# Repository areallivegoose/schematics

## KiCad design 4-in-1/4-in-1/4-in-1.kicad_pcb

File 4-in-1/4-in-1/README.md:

Each board on a separate schematic, with power on main sheet.
Effect order: DynaComp > Rangemaster > OCD > LPB1

Sources:
+ [Ross DynaComp](https://www.electrosmash.com/mxr-dyna-comp-analysis)
+ [Dallas Rangemaster](https://fuzzcentral.ssguitar.com/rangemaster.php)
+ [Fulltone OCD](http://zadvitsky.com/index.php/projects/pedals/ocd-overdrive-diy.html)
+ [LPB1](https://www.coda-effects.com/p/lpb1-circuit-analysis.html)

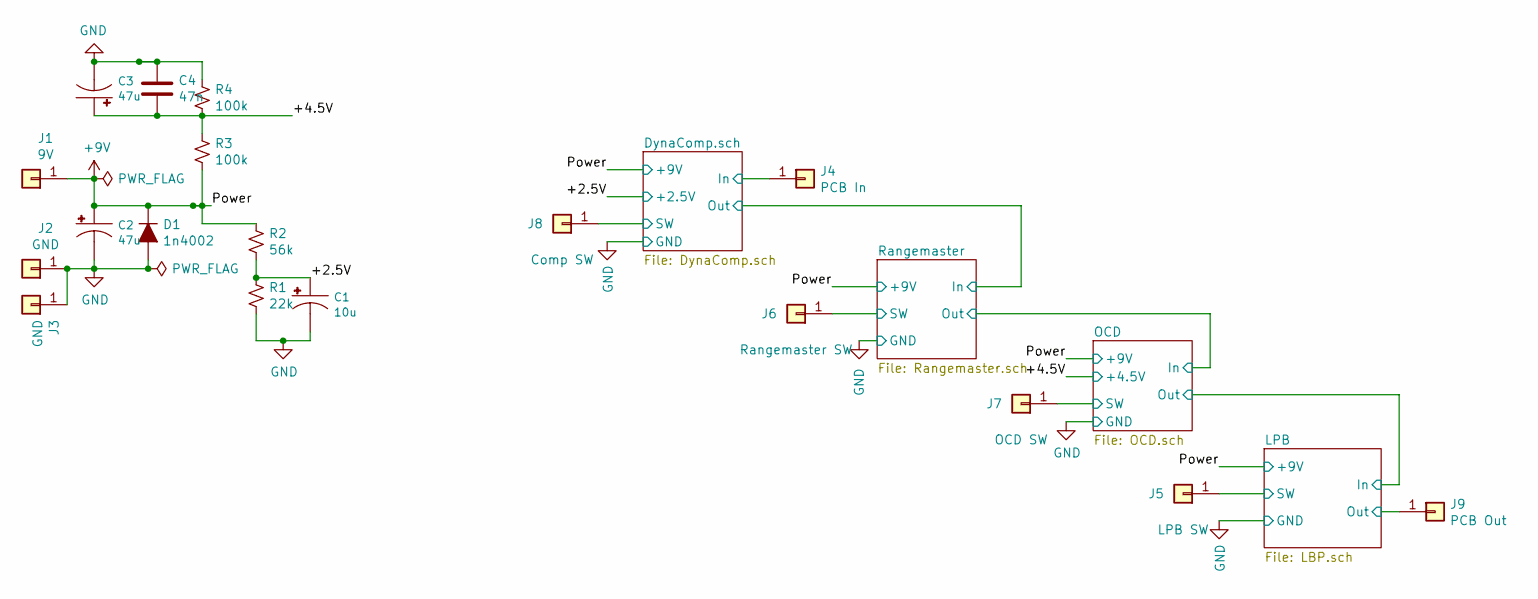
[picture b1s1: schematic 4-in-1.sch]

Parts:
C1: 10u; Cap_Electrolytic_TH
C2, C3: 47u; Cap_Electrolytic_TH
C4: 47n; Cap_Ceramic_TH
D1: 1n4002; Diode_BAT-85S_TH
J1: 9V; WireHole
J2, J3: GND; WireHole
J4: PCB In; WireHole
J5: LPB SW; WireHole
J6: Rangemaster SW; WireHole
J7: OCD SW; WireHole
J8: Comp SW; WireHole
J9: PCB Out; WireHole
R1: 22k; R_Axial_DIN0207_L6.3mm_D2.5mm_P7.62mm_Horizontal
R2: 56k; R_Axial_DIN0207_L6.3mm_D2.5mm_P7.62mm_Horizontal
R3, R4: 100k; R_Axial_DIN0207_L6.3mm_D2.5mm_P7.62mm_Horizontal

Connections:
+9V: C2.1 (+), D1.1 (K), J1.1, R2.1, R3.2; also elsewhere on the board
/+2.5V: C1.1 (+), R1.1, R2.2; also elsewhere on the board
/+4.5V: C3.1 (+), C4.2, R3.1, R4.2; also elsewhere on the board
/DynaComp.sch/In: J4.1; also elsewhere on the board
/DynaComp.sch/SW: J8.1; also elsewhere on the board
/LPB/Out: J9.1; also elsewhere on the board
/LPB/SW: J5.1; also elsewhere on the board
/OCD/SW: J7.1; also elsewhere on the board
/Rangemaster/SW: J6.1; also elsewhere on the board
GND: C1.2 (-), C2.2 (-), C3.2 (-), C4.1, D1.2 (A), J2.1, J3.1, R1.2, R4.1; also elsewhere on the board

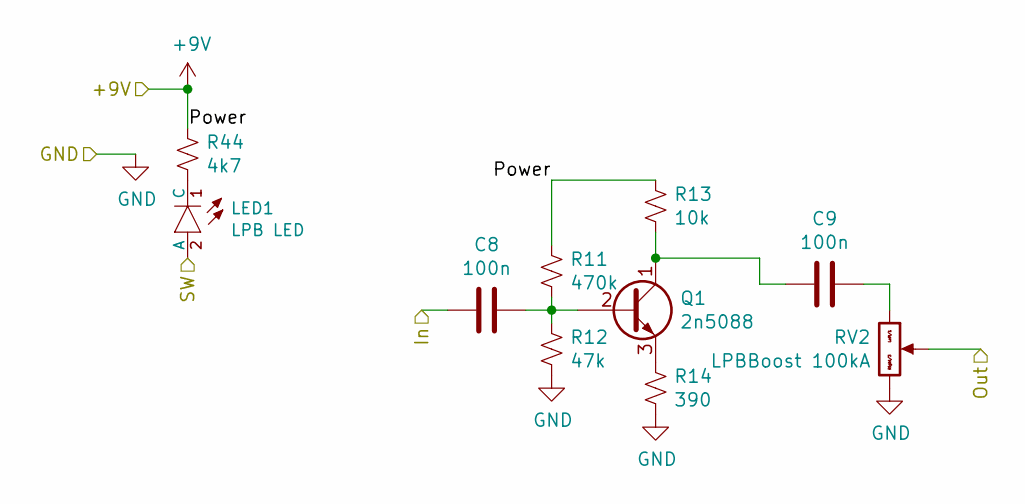
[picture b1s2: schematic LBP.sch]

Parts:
C8, C9: 100n; Cap_Ceramic_TH
LED1: LPB LED; LED-C1-A2-3MM-VERT
Q1: 2n5088; TO-92_Inline_Wide
R11: 470k; R_Axial_DIN0207_L6.3mm_D2.5mm_P7.62mm_Horizontal
R12: 47k; R_Axial_DIN0207_L6.3mm_D2.5mm_P7.62mm_Horizontal
R13: 10k; R_Axial_DIN0207_L6.3mm_D2.5mm_P7.62mm_Horizontal
R14: 390; R_Axial_DIN0207_L6.3mm_D2.5mm_P7.62mm_Horizontal
R44: 4k7; R_Axial_DIN0207_L6.3mm_D2.5mm_P7.62mm_Horizontal
RV2: LPBBoost 100kA; Pot_16mm_NoDet_RV16AF-4A

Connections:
+9V: R11.2, R13.1, R44.1; also elsewhere on the board
/LPB/In: C8.2; also elsewhere on the board
/LPB/Out: RV2.2 (Center); also elsewhere on the board
/LPB/SW: LED1.2 (A); also elsewhere on the board
GND: R12.2, R14.2, RV2.3 (Right); also elsewhere on the board
unnamed: C8.1, Q1.2 (B), R11.1, R12.1
unnamed: C9.1, RV2.1 (Left)
unnamed: C9.2, Q1.1 (C), R13.2
unnamed: LED1.1 (C), R44.2
unnamed: Q1.3 (E), R14.1

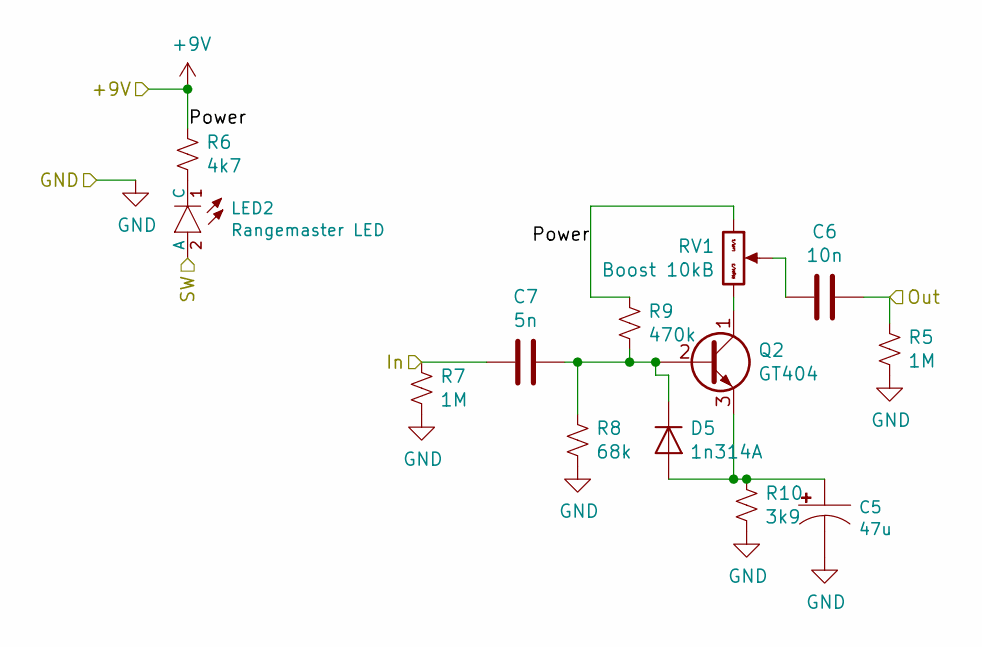
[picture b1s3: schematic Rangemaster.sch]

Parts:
C5: 47u; Cap_Electrolytic_TH
C6: 10n; Cap_Ceramic_TH
C7: 5n; Cap_Ceramic_TH
D5: 1n314A; Diode_BAT-85S_TH
LED2: Rangemaster LED; LED-C1-A2-3MM-VERT
Q2: GT404; TO-92_Inline
R5, R7: 1M; R_Axial_DIN0207_L6.3mm_D2.5mm_P7.62mm_Horizontal
R6: 4k7; R_Axial_DIN0207_L6.3mm_D2.5mm_P7.62mm_Horizontal
R8: 68k; R_Axial_DIN0207_L6.3mm_D2.5mm_P7.62mm_Horizontal
R9: 470k; R_Axial_DIN0207_L6.3mm_D2.5mm_P7.62mm_Horizontal
R10: 3k9; R_Axial_DIN0207_L6.3mm_D2.5mm_P7.62mm_Horizontal
RV1: Boost 10kB; Pot_16mm_NoDet_RV16AF-4A

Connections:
+9V: R6.1, R9.1, RV1.1 (Left); also elsewhere on the board
/OCD/In: C6.1, R5.1; also elsewhere on the board
/Rangemaster/In: C7.2, R7.1; also elsewhere on the board
/Rangemaster/SW: LED2.2 (A); also elsewhere on the board
GND: C5.2 (-), R5.2, R7.2, R8.2, R10.2; also elsewhere on the board
unnamed: C5.1 (+), D5.2 (A), Q2.3 (E), R10.1
unnamed: C6.2, RV1.2 (Center)
unnamed: C7.1, D5.1 (K), Q2.2 (B), R8.1, R9.2
unnamed: LED2.1 (C), R6.2
unnamed: Q2.1 (C), RV1.3 (Right)

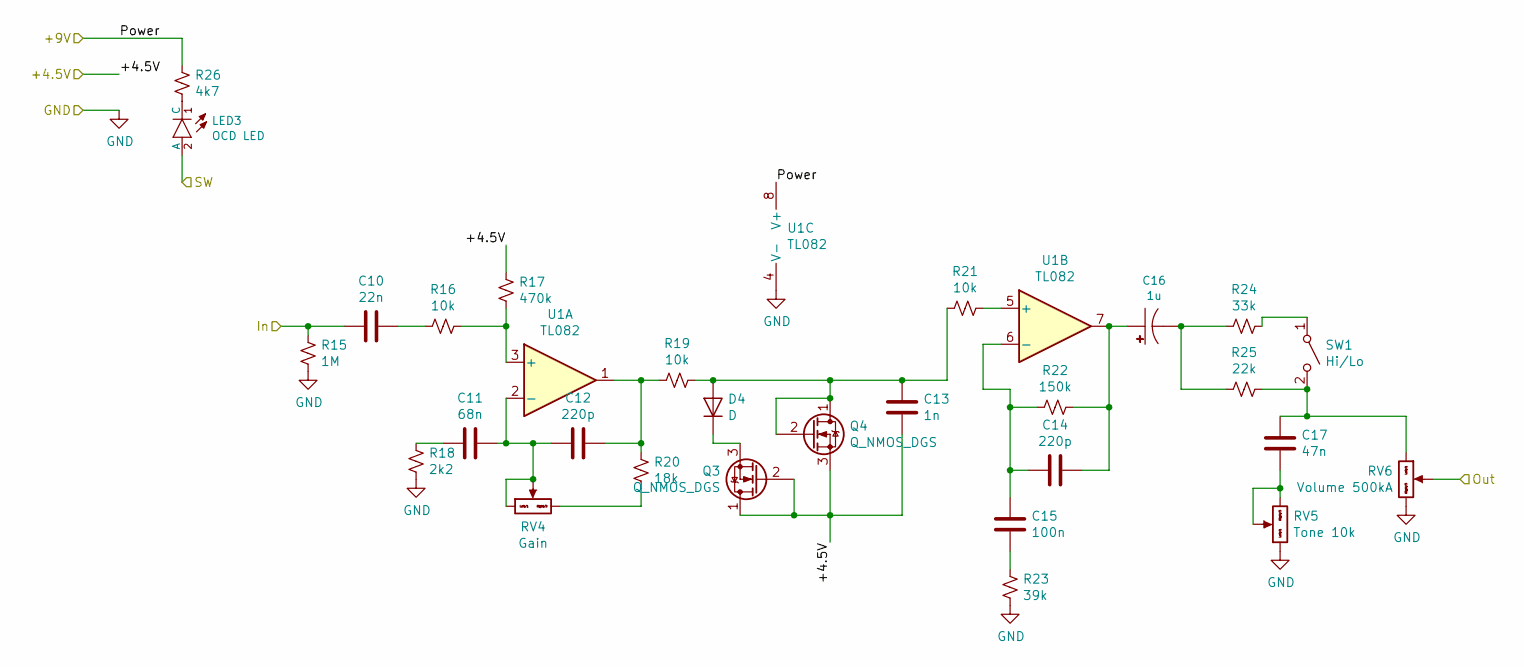
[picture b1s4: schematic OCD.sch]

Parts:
C10: 22n; Cap_Ceramic_TH
C11: 68n; Cap_Ceramic_TH
C12, C14: 220p; Cap_Ceramic_TH
C13: 1n; Cap_Ceramic_TH
C15: 100n; Cap_Ceramic_TH
C16: 1u; Cap_Electrolytic_TH
C17: 47n; Cap_Ceramic_TH
D4: D; Diode_BAT-85S_TH
LED3: OCD LED; LED-C1-A2-3MM-VERT
Q3, Q4: Q_NMOS_DGS; TO-92_Inline
R15: 1M; R_Axial_DIN0207_L6.3mm_D2.5mm_P7.62mm_Horizontal
R16, R19, R21: 10k; R_Axial_DIN0207_L6.3mm_D2.5mm_P7.62mm_Horizontal
R17: 470k; R_Axial_DIN0207_L6.3mm_D2.5mm_P7.62mm_Horizontal
R18: 2k2; R_Axial_DIN0207_L6.3mm_D2.5mm_P7.62mm_Horizontal
R20: 18k; R_Axial_DIN0207_L6.3mm_D2.5mm_P7.62mm_Horizontal
R22: 150k; R_Axial_DIN0207_L6.3mm_D2.5mm_P7.62mm_Horizontal
R23: 39k; R_Axial_DIN0207_L6.3mm_D2.5mm_P7.62mm_Horizontal
R24: 33k; R_Axial_DIN0207_L6.3mm_D2.5mm_P7.62mm_Horizontal
R25: 22k; R_Axial_DIN0207_L6.3mm_D2.5mm_P7.62mm_Horizontal
R26: 4k7; R_Axial_DIN0207_L6.3mm_D2.5mm_P7.62mm_Horizontal
RV4: Gain; Pot_16mm_NoDet_RV16AF-4A
RV5: Tone 10k; Pot_16mm_NoDet_RV16AF-4A
RV6: Volume 500kA; Pot_16mm_NoDet_RV16AF-4A
SW1: Hi/Lo; SPST-SUB
U1: TL082; DIP_8pin_TL072_TH

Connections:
+9V: R26.1, U1.8 (V+); also elsewhere on the board
/+4.5V: C13.2, Q3.1 (D), Q3.2 (G), Q4.3 (S), R17.1; also elsewhere on the board
/LPB/In: RV6.2 (Center); also elsewhere on the board
/OCD/In: C10.2, R15.1; also elsewhere on the board
/OCD/SW: LED3.2 (A); also elsewhere on the board
GND: R15.2, R18.2, R23.2, RV5.1 (Left), RV6.3 (Right), U1.4 (V-); also elsewhere on the board
unnamed: C10.1, R16.2
unnamed: C11.1, C12.2, RV4.1 (Left), RV4.2 (Center), U1.2 (-)
unnamed: C11.2, R18.1
unnamed: C12.1, R19.2, R20.1, U1.1
unnamed: C13.1, D4.2 (A), Q4.1 (D), Q4.2 (G), R19.1, R21.2
unnamed: C14.1, C16.1 (+), R22.1, U1.7
unnamed: C14.2, C15.2, R22.2, U1.6 (-)
unnamed: C15.1, R23.1
unnamed: C16.2 (-), R24.2, R25.2
unnamed: C17.1, R25.1, RV6.1 (Left), SW1.2 (B)
unnamed: C17.2, RV5.2 (Center), RV5.3 (Right)
unnamed: D4.1 (K), Q3.3 (S)
unnamed: LED3.1 (C), R26.2
unnamed: R16.1, R17.2, U1.3 (+)
unnamed: R20.2, RV4.3 (Right)
unnamed: R21.1, U1.5 (+)
unnamed: R24.1, SW1.1 (A)

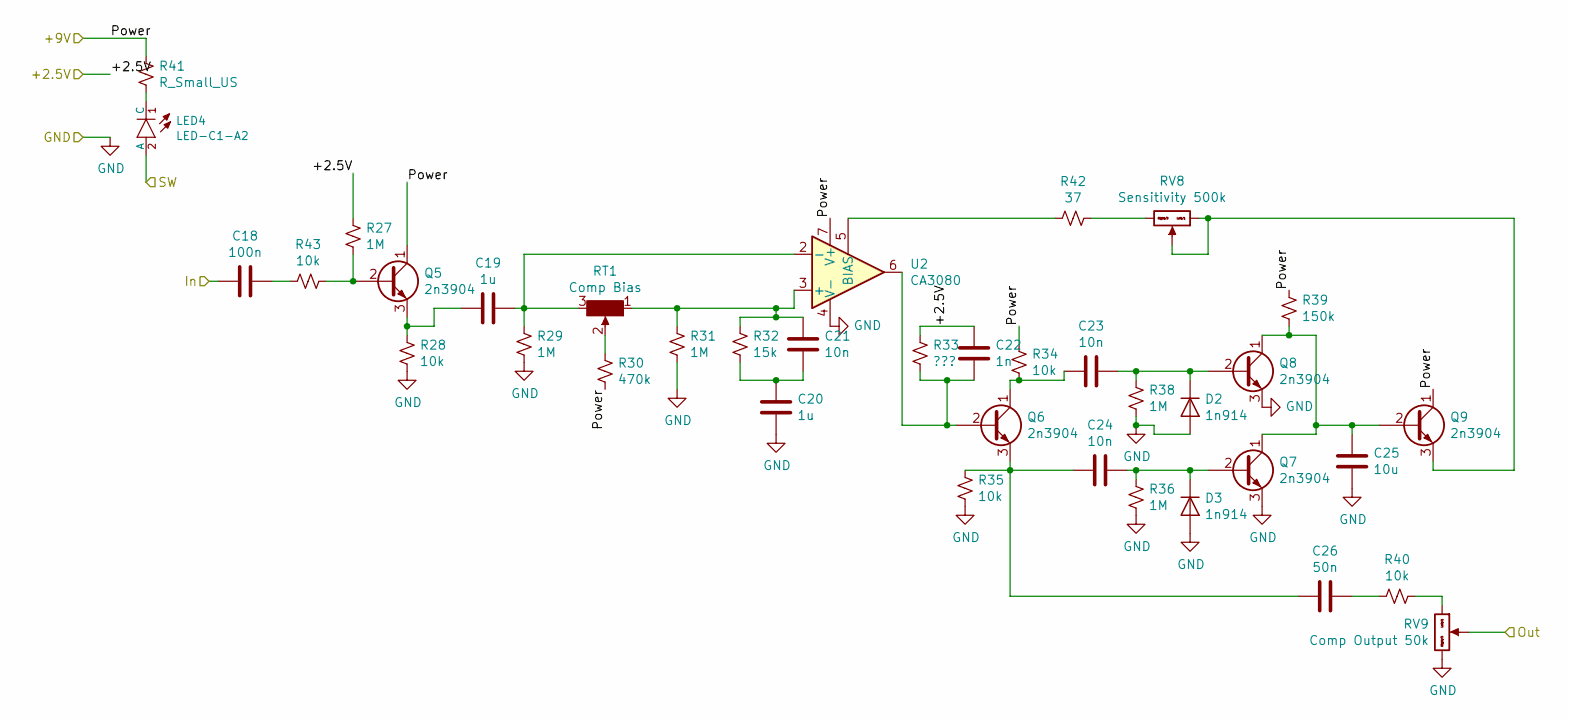
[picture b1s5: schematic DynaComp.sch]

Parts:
C18: 100n; Cap_Ceramic_TH
C19, C20: 1u; Cap_Ceramic_TH
C21, C23, C24: 10n; Cap_Ceramic_TH
C22: 1n; Cap_Ceramic_TH
C25: 10u; Cap_Ceramic_TH
C26: 50n; Cap_Ceramic_TH
D2, D3: 1n914; Diode_BAT-85S_TH
LED4: LED-C1-A2; LED-C1-A2-3MM-VERT
Q5, Q6, Q7, Q8, Q9: 2n3904; TO-92_Inline
R27, R29, R31, R36, R38: 1M; R_Axial_DIN0207_L6.3mm_D2.5mm_P7.62mm_Horizontal
R28, R34, R35, R40, R43: 10k; R_Axial_DIN0207_L6.3mm_D2.5mm_P7.62mm_Horizontal
R30: 470k; R_Axial_DIN0207_L6.3mm_D2.5mm_P7.62mm_Horizontal
R32: 15k; R_Axial_DIN0207_L6.3mm_D2.5mm_P7.62mm_Horizontal
R33: ???; R_Axial_DIN0207_L6.3mm_D2.5mm_P7.62mm_Horizontal
R39: 150k; R_Axial_DIN0207_L6.3mm_D2.5mm_P7.62mm_Horizontal
R41: R_Small_US; R_Axial_DIN0207_L6.3mm_D2.5mm_P7.62mm_Horizontal
R42: 37; R_Axial_DIN0207_L6.3mm_D2.5mm_P7.62mm_Horizontal
RT1: Comp Bias; Trim_Round_Black_Small
RV8: Sensitivity 500k; Pot_16mm_NoDet_RV16AF-4A
RV9: Comp Output 50k; Pot_16mm_NoDet_RV16AF-4A
U2: CA3080; DIP_8pin_TL072_TH

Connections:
+9V: Q5.1 (C), Q9.1 (C), R30.2, R34.1, R39.1, R41.1, U2.7 (V+); also elsewhere on the board
/+2.5V: C22.1, R27.2, R33.1; also elsewhere on the board
/DynaComp.sch/In: C18.2; also elsewhere on the board
/DynaComp.sch/SW: LED4.2 (A); also elsewhere on the board
/Rangemaster/In: RV9.2 (Center); also elsewhere on the board
GND: C20.2, C25.2, D2.2 (A), D3.2 (A), Q7.3 (E), Q8.3 (E), R28.2, R29.2, R31.2, R35.2, R36.2, R38.2, RV9.3 (Right), U2.4 (V-); also elsewhere on the board
unnamed: C18.1, R43.2
unnamed: C19.1, R29.1, RT1.3 (Right), U2.2 (-)
unnamed: C19.2, Q5.3 (E), R28.1
unnamed: C20.1, C21.2, R32.2
unnamed: C21.1, R31.1, R32.1, RT1.1 (Left), U2.3 (+)
unnamed: C22.2, Q6.2 (B), R33.2, U2.6
unnamed: C23.1, D2.1 (K), Q8.2 (B), R38.1
unnamed: C23.2, Q6.1 (C), R34.2
unnamed: C24.1, D3.1 (K), Q7.2 (B), R36.1
unnamed: C24.2, C26.2, Q6.3 (E), R35.1
unnamed: C25.1, Q7.1 (C), Q8.1 (C), Q9.2 (B), R39.2
unnamed: C26.1, R40.2
unnamed: LED4.1 (C), R41.2
unnamed: Q5.2 (B), R27.1, R43.1
unnamed: Q9.3 (E), RV8.1 (Left), RV8.2 (Center)
unnamed: R30.1, RT1.2 (Center)
unnamed: R40.1, RV9.1 (Left)
unnamed: R42.1, RV8.3 (Right)
unnamed: R42.2, U2.5 (BIAS)

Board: 2 copper layers, 107 parts (8 on the bottom side), 59 nets, no tracks yet.

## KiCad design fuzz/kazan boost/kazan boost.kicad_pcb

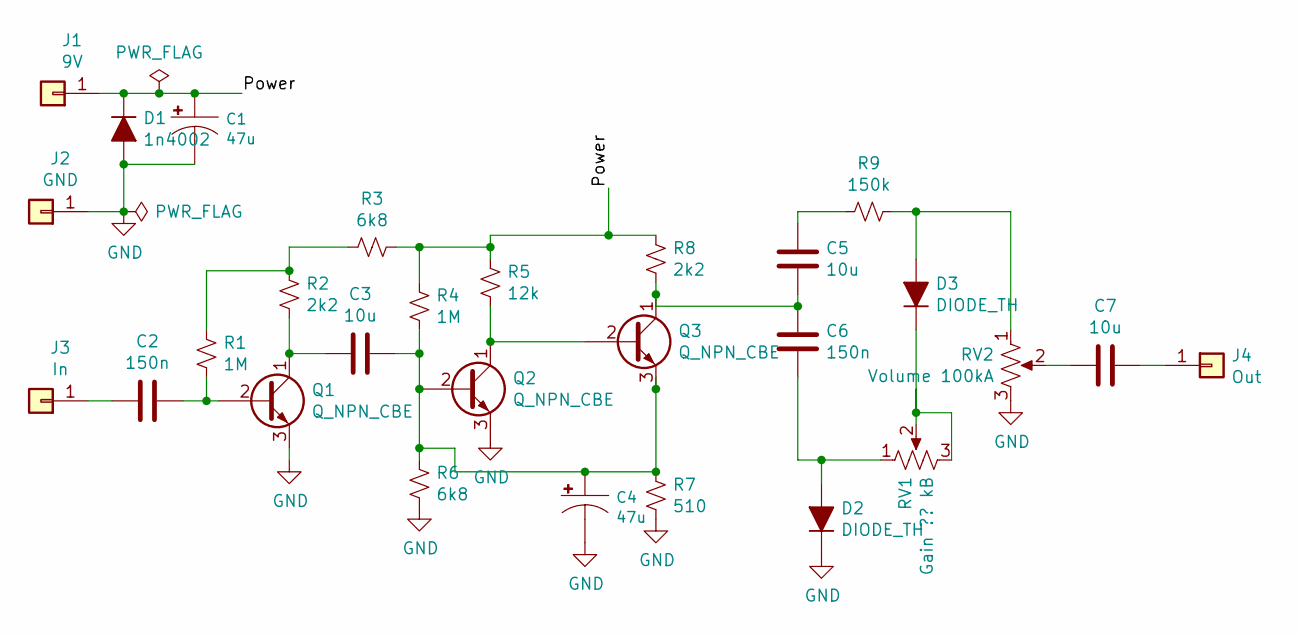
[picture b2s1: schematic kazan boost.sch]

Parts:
C1, C4: 47u; Cap_Electrolytic_TH
C2, C6: 150n; Cap_Ceramic_TH
C3, C5, C7: 10u; Cap_Ceramic_TH
D1: 1n4002; Diode_BAT-85S_TH
D2, D3: DIODE_TH; Diode_BAT-85S_TH
J1: 9V; WireHole
J2: GND; WireHole
J3: In; WireHole
J4: Out; WireHole
Q1, Q2, Q3: Q_NPN_CBE; TO-92_Inline_Wide
R1, R4: 1M; R_Axial_DIN0207_L6.3mm_D2.5mm_P7.62mm_Horizontal
R2, R8: 2k2; R_Axial_DIN0207_L6.3mm_D2.5mm_P7.62mm_Horizontal
R3, R6: 6k8; R_Axial_DIN0207_L6.3mm_D2.5mm_P7.62mm_Horizontal
R5: 12k; R_Axial_DIN0207_L6.3mm_D2.5mm_P7.62mm_Horizontal
R7: 510; R_Axial_DIN0207_L6.3mm_D2.5mm_P7.62mm_Horizontal
R9: 150k; R_Axial_DIN0207_L6.3mm_D2.5mm_P7.62mm_Horizontal
RV1: Gain ?? kB; Pot_16mm_NoDet_RV16AF-4A
RV2: Volume 100kA; Pot_16mm_NoDet_RV16AF-4A

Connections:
/Power: C1.1 (+), D1.1 (K), J1.1, R3.1, R4.2, R5.2, R8.1
GND: C1.2 (-), C4.2 (-), D1.2 (A), D2.1 (K), J2.1, Q1.3 (E), Q2.3 (E), R6.2, R7.2, RV2.3
unnamed: C2.1, Q1.2 (B), R1.2
unnamed: C2.2, J3.1
unnamed: C3.1, C4.1 (+), Q2.2 (B), Q3.3 (E), R4.1, R6.1, R7.1
unnamed: C3.2, Q1.1 (C), R2.2
unnamed: C5.1, R9.2
unnamed: C5.2, C6.1, Q3.1 (C), R8.2
unnamed: C6.2, D2.2 (A), RV1.1
unnamed: C7.1, J4.1
unnamed: C7.2, RV2.2
unnamed: D3.1 (K), RV1.2, RV1.3
unnamed: D3.2 (A), R9.1, RV2.1
unnamed: Q2.1 (C), Q3.2 (B), R5.1
unnamed: R1.1, R2.1, R3.2

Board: 2 copper layers, 28 parts (2 on the bottom side), 15 nets, no tracks yet.

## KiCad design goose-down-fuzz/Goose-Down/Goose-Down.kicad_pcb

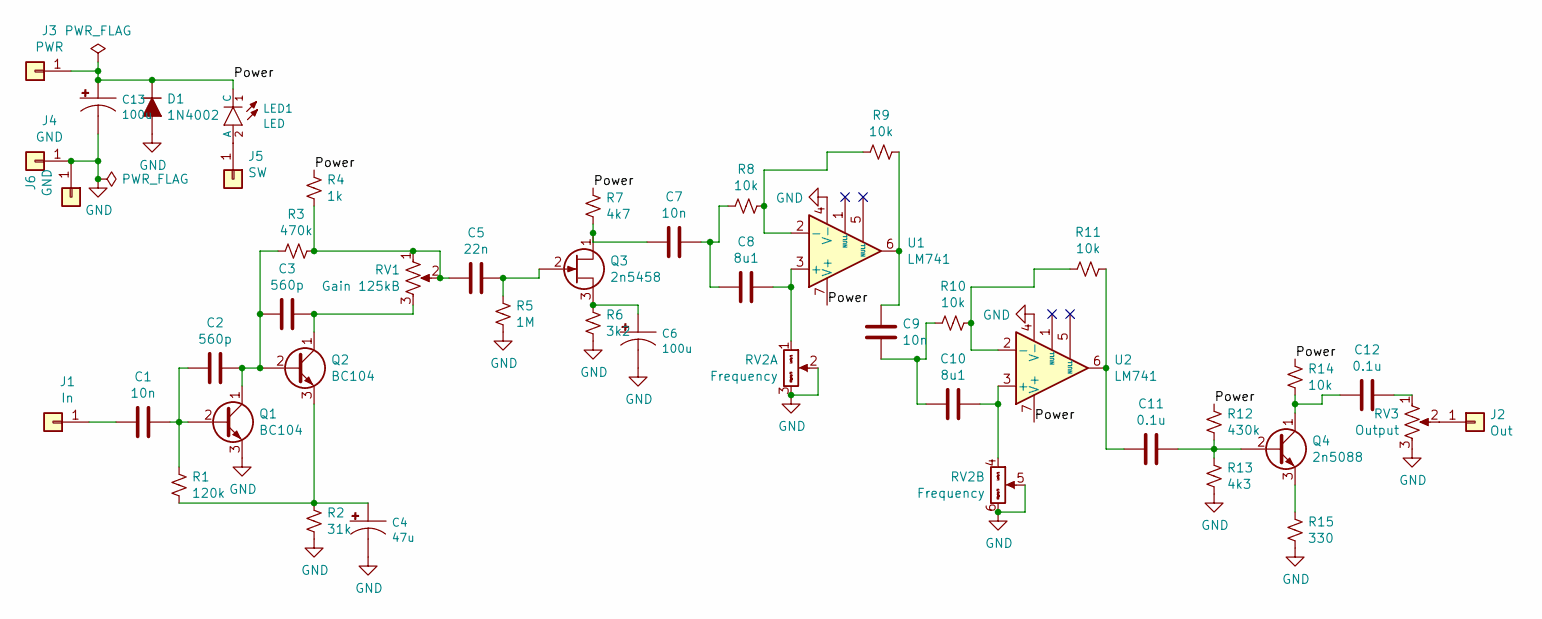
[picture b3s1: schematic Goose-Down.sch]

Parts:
C1, C7, C9: 10n; Cap_Ceramic_TH
C2, C3: 560p; Cap_Ceramic_TH
C4: 47u; Cap_Electrolytic_TH
C5: 22n; Cap_Ceramic_TH
C6, C13: 100u; Cap_Electrolytic_TH
C8, C10: 8u1; Cap_Ceramic_TH
C11, C12: 0.1u; Cap_Ceramic_TH
D1: 1N4002; Diode_BAT-85S_TH
J1: In; Wire_12AWG
J2: Out; Wire_12AWG
J3: PWR; Wire_12AWG
J4, J6: GND; Wire_12AWG
J5: SW; Wire_12AWG
LED1: LED; LED-C1-A2-3MM-VERT
Q1, Q2: BC104; TO-92
Q3: 2n5458; TO-92
Q4: 2n5088; TO-92
R1: 120k; R_Axial_DIN0207_L6.3mm_D2.5mm_P7.62mm_Horizontal
R2: 31k; R_Axial_DIN0207_L6.3mm_D2.5mm_P7.62mm_Horizontal
R3: 470k; R_Axial_DIN0207_L6.3mm_D2.5mm_P7.62mm_Horizontal
R4: 1k; R_Axial_DIN0207_L6.3mm_D2.5mm_P7.62mm_Horizontal
R5: 1M; R_Axial_DIN0207_L6.3mm_D2.5mm_P7.62mm_Horizontal
R6: 3k2; R_Axial_DIN0207_L6.3mm_D2.5mm_P7.62mm_Horizontal
R7: 4k7; R_Axial_DIN0207_L6.3mm_D2.5mm_P7.62mm_Horizontal
R8, R9, R10, R11, R14: 10k; R_Axial_DIN0207_L6.3mm_D2.5mm_P7.62mm_Horizontal
R12: 430k; R_Axial_DIN0207_L6.3mm_D2.5mm_P7.62mm_Horizontal
R13: 4k3; R_Axial_DIN0207_L6.3mm_D2.5mm_P7.62mm_Horizontal
R15: 330; R_Axial_DIN0207_L6.3mm_D2.5mm_P7.62mm_Horizontal
RV1: Gain 125kB; Pot_16mm_NoDet_RV16AF-4A
RV2: Frequency; Pot_Dual_16mm_NoDet_RV16AF-4A
RV3: Output; Pot_16mm_NoDet_RV16AF-4A
U1, U2: LM741; DIP_8pin_TL072_TH

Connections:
/Power: C13.1 (+), D1.1 (K), J3.1, LED1.1 (C), R4.1, R7.1, R12.1, R14.1, U1.7 (V+), U2.7 (V+)
GND: C4.2 (-), C6.2 (-), C13.2 (-), D1.2 (A), J4.1, J6.1, Q1.3 (E), R2.2, R5.2, R6.2, R13.2, R15.2, RV2.2 (Center), RV2.3 (Right), RV2.5 (Center), RV2.6 (Right), RV3.3, U1.4 (V-), U2.4 (V-)
unnamed: C1.1, C2.2, Q1.2 (B), R1.1
unnamed: C1.2, J1.1
unnamed: C2.1, C3.2, Q1.1 (C), Q2.2 (B), R3.2
unnamed: C3.1, Q2.1 (C), RV1.3
unnamed: C4.1 (+), Q2.3 (E), R1.2, R2.1
unnamed: C5.1, Q3.2 (G), R5.1
unnamed: C5.2, R3.1, R4.2, RV1.1, RV1.2
unnamed: C6.1 (+), Q3.3 (S), R6.1
unnamed: C7.1, C8.2, R8.2
unnamed: C7.2, Q3.1 (D), R7.2
unnamed: C8.1, RV2.1 (Left), U1.3 (+)
unnamed: C9.1, R9.1, U1.6
unnamed: C10.1, RV2.4 (Left), U2.3 (+)
unnamed: C9.2, C10.2, R10.2
unnamed: C11.1, Q4.2 (B), R12.2, R13.1
unnamed: C11.2, R11.1, U2.6
unnamed: C12.1, RV3.1
unnamed: C12.2, Q4.1 (C), R14.2
unnamed: J2.1, RV3.2
unnamed: J5.1, LED1.2 (A)
unnamed: Q4.3 (E), R15.1
unnamed: R8.1, R9.2, U1.2 (-)
unnamed: R10.1, R11.2, U2.2 (-)

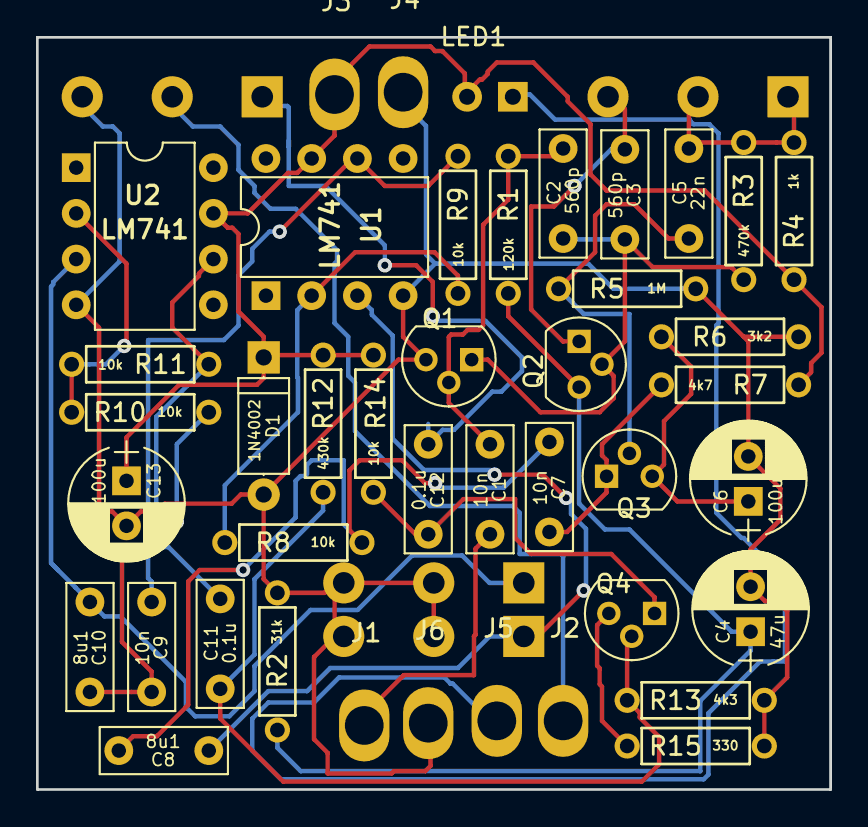
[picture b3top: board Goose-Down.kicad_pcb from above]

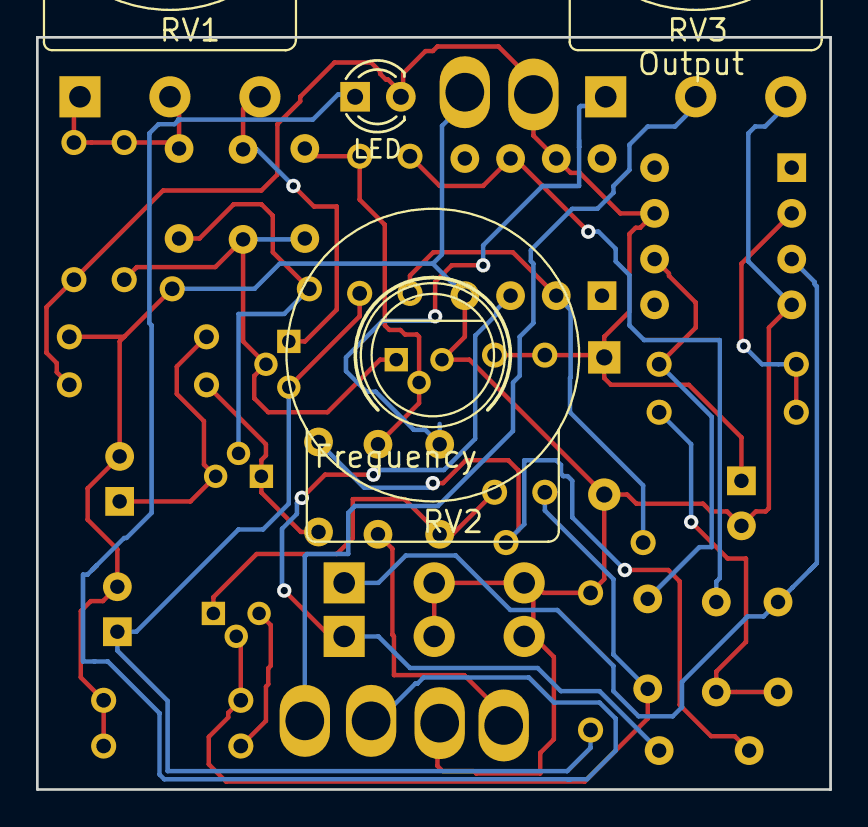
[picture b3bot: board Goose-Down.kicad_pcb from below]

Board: 2 copper layers, 44.1 x 41.8 mm, 45 parts (4 on the bottom side), 25 nets.

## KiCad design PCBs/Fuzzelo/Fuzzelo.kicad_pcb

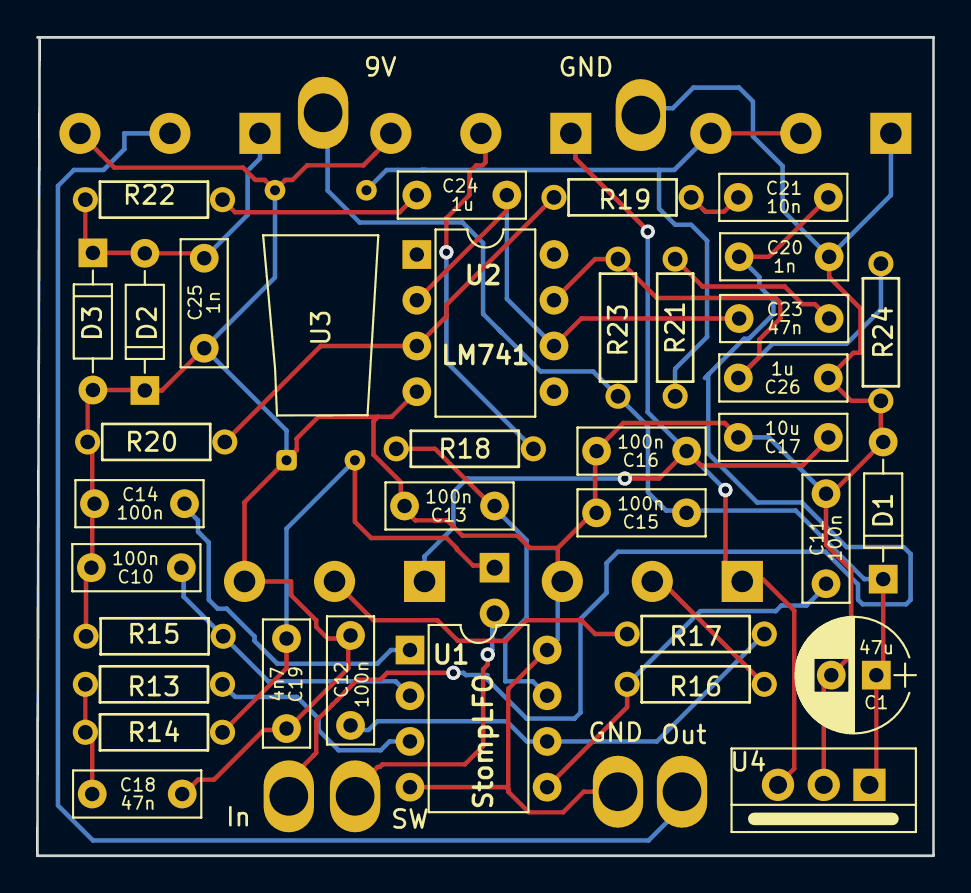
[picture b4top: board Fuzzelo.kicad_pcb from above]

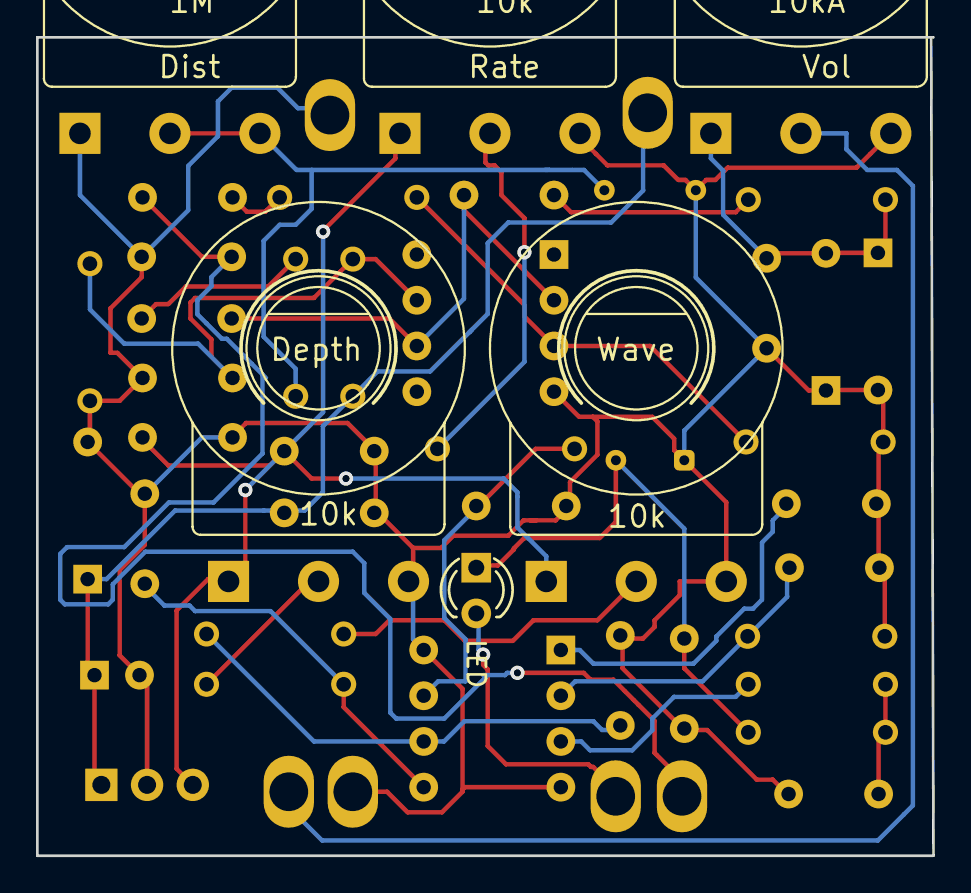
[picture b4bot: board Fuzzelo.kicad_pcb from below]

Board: 2 copper layers, 49.8 x 45.5 mm, 47 parts (5 on the bottom side), 24 nets.

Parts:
9V: Wire_12AWG
C1: 47u; Cap_Electrolytic_TH
C10, C11, C12, C13, C14, C15, C16: 100n; Cap_Ceramic_TH
C17: 10u; Cap_Ceramic_TH
C18, C23: 47n; Cap_Ceramic_TH
C19: 4n7; Cap_Ceramic_TH
C20, C25: 1n; Cap_Ceramic_TH
C21: 10n; Cap_Ceramic_TH
C24, C26: 1u; Cap_Ceramic_TH
D1, D2, D3: D_DO-35_P7.62mm_Horizontal
Depth: 10k; Pot_16mm_NoDet_RV16AF-4A
Dist: 1M; Pot_16mm_NoDet_RV16AF-4A
GND: Wire_12AWG
GND#2: Wire_12AWG
In: Wire_12AWG
Out: Wire_12AWG
R13, R14, R15, R16, R17, R18, R19, R20, R21, R22, R23, R24: R_Axial_DIN0207_L6.3mm_D2.5mm_P7.62mm_Horizontal
Rate: 10k; Pot_16mm_NoDet_RV16AF-4A
SW: Wire_12AWG
U1: StompLFO; DIP_8pin_TL072_TH
U2: LM741; DIP_8pin_TL072_TH
U3: VTL5C; PerkinElmer_VTL5C
U4: TO-220-3_Vertical
Vol: 10kA; Pot_16mm_NoDet_RV16AF-4A
Wave: 10k; Pot_16mm_NoDet_RV16AF-4A

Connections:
/+5V: C16.1, C17.1, Depth.1, Rate.1, U4.3, Wave.1
/PowerReg: 9V.1, C1.1, C15.1, D1.1, R23.2, U4.1
GND: C1.2, C10.2, C11.2, C12.2, C13.2, C14.1, C15.2, C16.2, C17.2, C18.2, C19.2, C20.2, C25.1, C26.1, D1.2, D2.2, D3.1, Depth.3, Dist.1, GND.1, GND#2.1, R15.2, R20.2, R24.1, Rate.3, U1.4, U1.8, U2.4, U3.1, U3.3, U4.2, Vol.3, Wave.3
unnamed: C10.1, R15.1, U1.2
unnamed: C11.1, R16.1, U1.5
unnamed: C12.1, R17.1, U1.6
unnamed: C13.1, R18.1, U1.7
unnamed: C14.2, U1.1
unnamed: C18.1, R13.1, R14.2
unnamed: C19.1, R14.1, U3.2
unnamed: C20.1, C21.2, In.1
unnamed: C21.1, R19.2
unnamed: C23.1, C24.2, U2.2, U2.6
unnamed: C23.2, R21.1
unnamed: C24.1, R22.1
unnamed: C25.2, D2.1, D3.2, R22.2, Vol.1
unnamed: C26.2, R23.1, R24.2, U2.7
unnamed: Depth.2, R16.2
unnamed: Dist.2, Dist.3, R21.2, U3.4
unnamed: Out.1, Vol.2
unnamed: R13.2, U1.3
unnamed: R17.2, Wave.2
unnamed: R18.2, Rate.2
unnamed: R19.1, R20.1, U2.3

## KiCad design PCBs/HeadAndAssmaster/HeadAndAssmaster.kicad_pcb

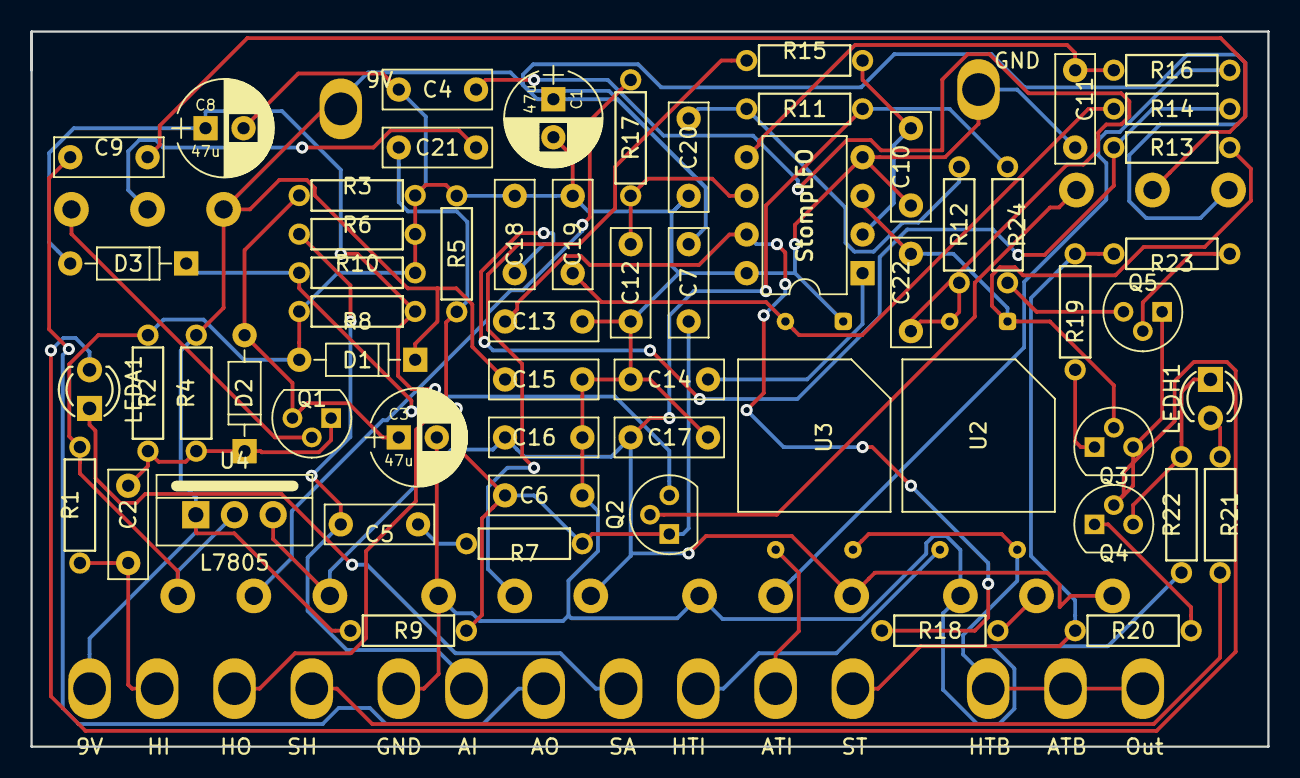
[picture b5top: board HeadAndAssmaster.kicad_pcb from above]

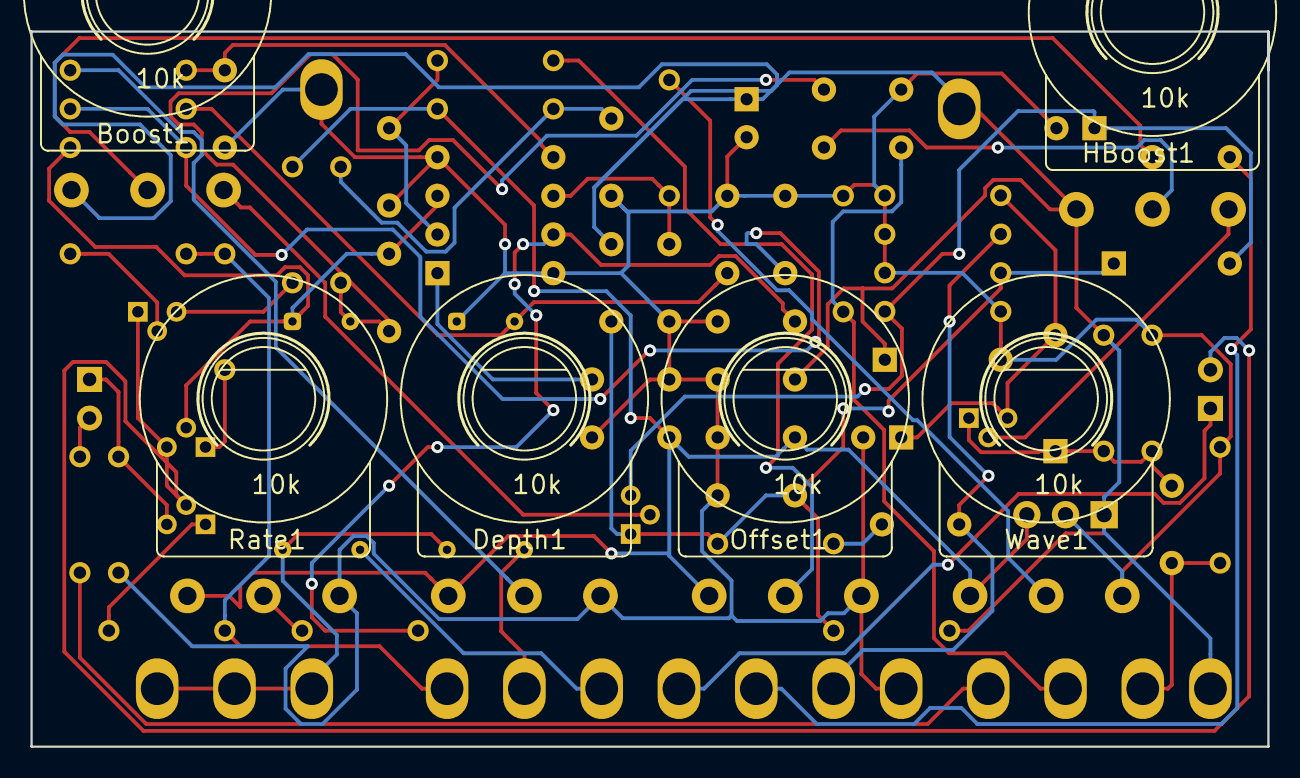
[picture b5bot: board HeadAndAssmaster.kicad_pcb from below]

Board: 2 copper layers, 81.3 x 47.0 mm, 79 parts (6 on the bottom side), 40 nets.

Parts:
9V, 9V#2: +9V; Wire_12AWG
AI: AssIn; Wire_12AWG
AO: AssOut; Wire_12AWG
ATB: AssTremBypass; Wire_12AWG
ATI: AssTremIn; Wire_12AWG
Boost1: 10k; Pot_16mm_NoDet_RV16AF-4A
C1, C3, C8: 47u; Cap_Electrolytic_TH
C2, C4, C5, C6, C7, C9, C10, C11, C12, C13, C14, C15, C16, C17, C18, C19, C20, C21, C22: C_Disc_P5.08mm
D1, D2, D3: D_DO-35_P7.62mm_Horizontal
Depth1: 10k; Pot_16mm_NoDet_RV16AF-4A
GND: GND; Wire_12AWG
GND#2: GND; Wire_12AWG
HBoost1: 10k; Pot_16mm_NoDet_RV16AF-4A
HI: HeadIn; Wire_12AWG
HO: HeadOut; Wire_12AWG
HTB: HTB1; Wire_12AWG
HTI: HeadTremIn; Wire_12AWG
Offset1: 10k; Pot_16mm_NoDet_RV16AF-4A
Out: Output; Wire_12AWG
Q1, Q2: NPN; TO-92
Q3, Q4: 2n2222; TO-92
Q5: 2n4403; TO-92
R1, R2, R3, R4, R5, R6, R7, R8, R9, R10, R11, R12, R13, R14, R15, R16, R17, R18, R19, R20, R21, R22, R23, R24: R_Axial_DIN0207_L6.3mm_D2.5mm_P7.62mm_Horizontal
Rate1: 10k; Pot_16mm_NoDet_RV16AF-4A
SA: SA; Wire_12AWG
SH: SH; Wire_12AWG
ST: ST; Wire_12AWG
U2, U3: VTL5C; PerkinElmer_VTL5C
U4: L7805; TO-220-3_Vertical
Wave1: 10k; Pot_16mm_NoDet_RV16AF-4A

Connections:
/+5V: C16.1, C17.1, Depth1.1, Offset1.1, R11.2, R24.1, Rate1.1, U4.3, Wave1.1
/PowerReg: 9V.1, 9V#2.1, Boost1.1, C1.1, C7.1, C15.1, D1.1, HBoost1.1, R4.1, R9.1, U4.1
/Tremolo: C22.1, Q3.2, R13.2, U2.1
/TremoloSwitched: Q3.3, Q4.2, Q5.1
GND: C1.2, C3.2, C6.2, C8.2, C10.2, C11.2, C12.2, C13.2, C14.1, C15.2, C16.2, C17.2, C18.2, C19.2, C20.2, C21.2, D1.2, Depth1.3, GND.1, GND#2.1, Offset1.3, R1.2, R2.2, R3.2, R5.2, R6.2, R8.2, R10.2, R22.2, Rate1.3, U3.1, U4.2, Wave1.3
unnamed: AI.1, C5.2, R6.1
unnamed: AO.1, C9.1
unnamed: ATB.1, HTB.1, Out.1, U2.3, U3.3
unnamed: ATI.1, U3.4
unnamed: Boost1.2, C9.2
unnamed: Boost1.3, Q2.2
unnamed: C2.1, D2.1, Q1.1, R2.1, R4.2
unnamed: C2.2, HI.1, R1.1
unnamed: C3.1, D2.2, Q1.3, R3.1
unnamed: C4.1, HO.1, R5.1
unnamed: C4.2, HBoost1.2
unnamed: C5.1, R7.2
unnamed: C6.1, C7.2, D3.1, Q2.1, R7.1, R8.1, R9.2
unnamed: C8.1, D3.2, Q2.3, R10.1
unnamed: C10.1, R15.1
unnamed: C11.1, R16.1
unnamed: C12.1, R17.1
unnamed: C13.1, R18.1
unnamed: C18.1, R13.1, R14.2
unnamed: C19.1, R14.1, U3.2
unnamed: C20.1, R11.1, R12.2
unnamed: C21.1, C22.2, R12.1, U2.2
unnamed: Depth1.2, R16.2
unnamed: HBoost1.3, Q1.2
unnamed: HTI.1, U2.4
unnamed: Q4.3, R22.1
unnamed: Offset1.2, R15.2
unnamed: Q3.1, R19.2
unnamed: Q4.1, R20.2
unnamed: Q5.2, R23.2
unnamed: Q5.3, R24.2
unnamed: R17.2, Wave1.2
unnamed: R18.2, Rate1.2
unnamed: R19.1, R20.1, R23.1, ST.1
unnamed: R21.1, SH.1

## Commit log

2019-04-16 Initial commit: fuzz, distortion and modulation current projects
2019-04-16 Add template BOM
2019-05-14 Add distortion and fuzz
    Add inventory [parts.md]
2019-05-14 UPdate parts format
2019-05-14 Fix list formatting
2019-05-14 Add TI OpAmp Handbook
2019-05-14 Add StompFLO docs
2019-06-18 Update parts
2019-06-18 Add graphics
2019-06-18 Removed elaine's work
2019-06-23 Add final graphics for Right in the Head and Ass
2019-06-23 Adds LTSpice folder with circuits
2019-06-23 Add KiCAD folder with PCBs
2019-06-24 Format parts/Capacitor section properly
2019-07-05 Add new shipment of ICs (charge pump, regulator, VCA)
2019-07-08 Add capacitors
2019-07-08 Add fuzzelo PCB
2019-07-08 Add gitignore
2019-07-08 Add Goose-Down fuzz
2019-07-08 Updated goose-down fuzz
2019-07-09 Add Goose-Down kicad files
2019-07-09 Add BOM for Goose Down
2019-07-09 Update tracks
2019-07-09 Update GD with Var-resistor Gain wiring, add Tone Stack to LTSpice plot
2019-07-10 Adds 4-in-1 board with sub-schematics.
    Each board on a separate schematic, with power on main sheet.
    Effect order: DynaComp > Rangemaster > OCD > LPB1
2019-07-10 Create README for 4-in-1
2019-07-12 Add kazan boost
